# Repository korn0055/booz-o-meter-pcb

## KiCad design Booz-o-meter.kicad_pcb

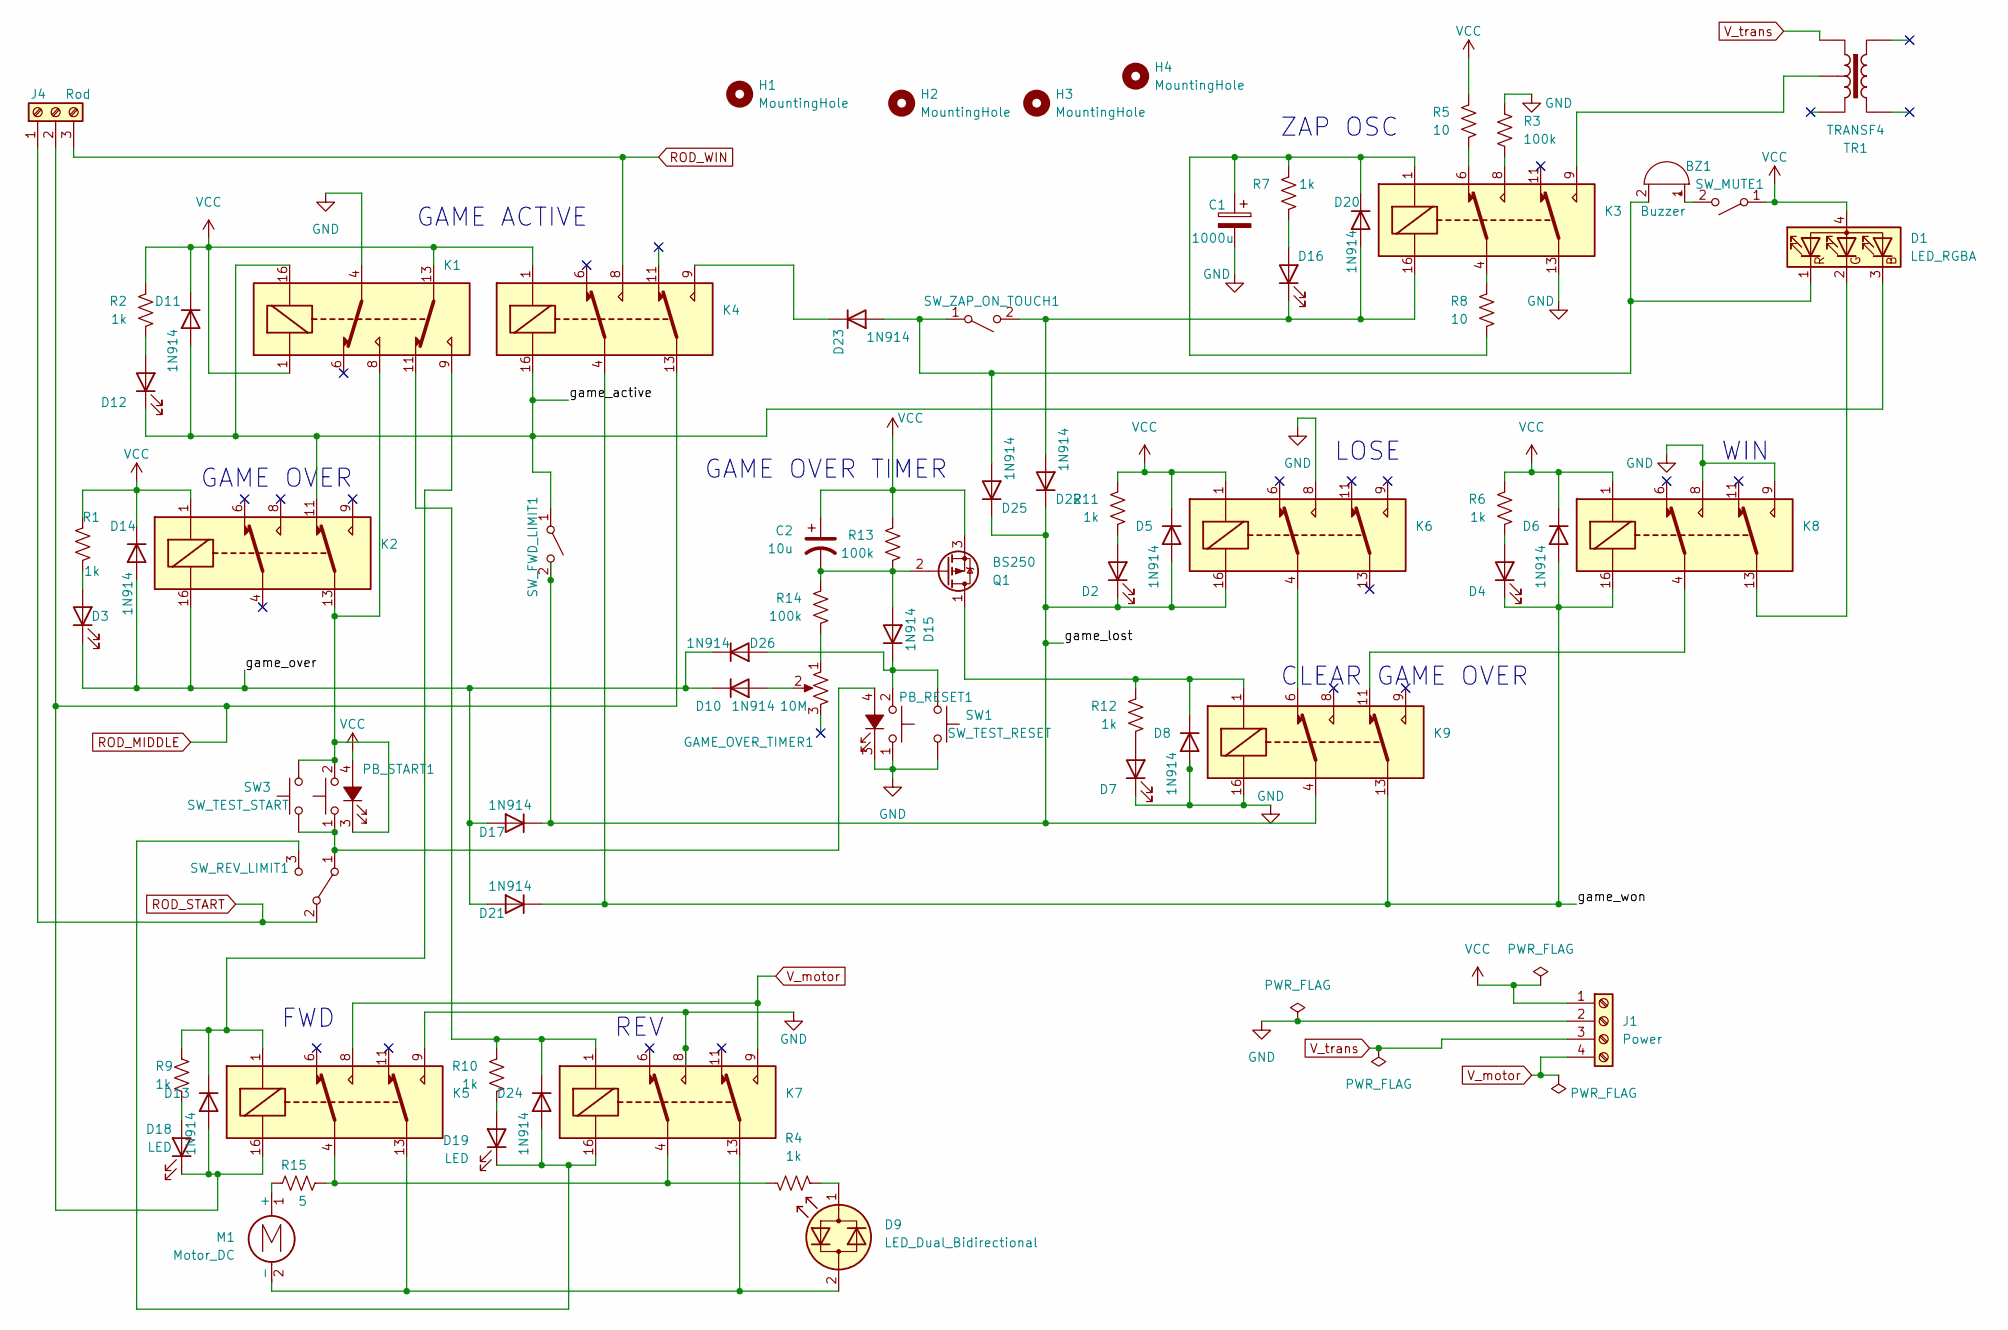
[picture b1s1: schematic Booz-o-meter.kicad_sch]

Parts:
BZ1: Buzzer; TerminalBlock_Phoenix_MKDS-1,5-2-5.08_1x02_P5.08mm_Horizont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
C1: 1000u; C_Radial_D10.0mm_H20.0mm_P5.00mm
C2: 10u; CP_Radial_Tantal_D5.0mm_P5.00mm
D1: LED_RGBA; TerminalBlock_Phoenix_MKDS-1,5-4-5.08_1x04_P5.08mm_Horizont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
D2, D3, D4, D7, D12, D16, D18, D19: LED; LED_D3.0mm
D5, D6, D8, D10, D11, D13, D14, D15, D17, D20, D21, D22, D23, D24, D25, D26: 1N914; D_DO-35_SOD27_P7.62mm_Horizontal
D9: LED_Dual_Bidirectional; LED_D5.0mm
GAME_OVER_TIMER1: 10M; Potentiometer_Bourns_3386P_Vertical
H1, H2, H3, H4: MountingHole; MountingHole_3.5mm
J1: Power; TerminalBlock_Phoenix_MKDS-1,5-4-5.08_1x04_P5.08mm_Horizont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
J4: Rod; TerminalBlock_Phoenix_MKDS-1,5-3-5.08_1x03_P5.08mm_Horizont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
K1, K2, K3, K4, K5, K6, K7, K8, K9: G5V-2; Relay_DPDT_Omron_G5V-2
M1: Motor_DC; TerminalBlock_Phoenix_MKDS-1,5-2-5.08_1x02_P5.08mm_Horizont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
PB_RESET1: SW_Push_LED; TerminalBlock_Phoenix_MKDS-1,5-4-5.08_1x04_P5.08mm_Horizont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
PB_START1: SW_Push_LED; TerminalBlock_Phoenix_MKDS-1,5-4-5.08_1x04_P5.08mm_Horizont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
Q1: BS250; TO-92_Inline
R1, R2, R4, R6, R7, R9, R10, R11, R12: 1k; R_Axial_DIN0207_L6.3mm_D2.5mm_P10.16mm_Horizontal
R3, R13, R14: 100k; R_Axial_DIN0207_L6.3mm_D2.5mm_P10.16mm_Horizontal
R5, R8: 10; R_Axial_DIN0207_L6.3mm_D2.5mm_P10.16mm_Horizontal
R15: 5; R_Axial_DIN0207_L6.3mm_D2.5mm_P10.16mm_Horizontal
SW1: SW_TEST_RESET; SW_PUSH_6mm
SW3: SW_TEST_START; SW_PUSH_6mm
SW_FWD_LIMIT1: SW_SPDT; TerminalBlock_Phoenix_MKDS-1,5-2-5.08_1x02_P5.08mm_Horizont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
SW_MUTE1: SW_SPST; TerminalBlock_Phoenix_MKDS-1,5-2-5.08_1x02_P5.08mm_Horizont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
SW_REV_LIMIT1: SW_SPDT; TerminalBlock_Phoenix_MKDS-1,5-3-5.08_1x03_P5.08mm_Horizont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
SW_ZAP_ON_TOUCH1: SW_SPST; TerminalBlock_Phoenix_MKDS-1,5-2-5.08_1x02_P5.08mm_Horizont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
TR1: TRANSF4; TerminalBlock_Phoenix_MKDS-1,5-2-5.08_1x02_P5.08mm_Horizont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

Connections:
/game_active: D1.3 (BK), D11.2 (A), D12.1 (K), K1.16, K2.11, K4.16, SW_FWD_LIMIT1.1 (A)
/game_lost: D2.1 (K), D5.2 (A), D17.1 (K), D22.1 (K), D25.1 (K), K6.16, K9.4, SW_FWD_LIMIT1.2 (B)
/game_over: D3.1 (K), D10.1 (K), D14.2 (A), D17.2 (A), D21.2 (A), D26.1 (K), K2.16
/game_won: D4.1 (K), D6.2 (A), D21.1 (K), K4.4, K8.16, K9.13
GND: C1.2, D7.1 (K), D8.2 (A), J1.2, K1.4, K3.13, K5.9, K6.8, K7.8, K8.8, K8.9, K9.16, PB_RESET1.1, PB_RESET1.3 (K), R3.1, SW1.2
unnamed: BZ1.2 (+), D1.1 (RK), D23.2 (A), D25.2 (A), SW_ZAP_ON_TOUCH1.1 (A)
unnamed: BZ1.1 (-), SW_MUTE1.2 (B)
unnamed: D1.2 (GK), K8.13
unnamed: D2.2 (A), R11.2
unnamed: D3.2 (A), R1.2
unnamed: D4.2 (A), R6.2
unnamed: D7.2 (A), R12.2
unnamed: D8.1 (K), K9.1, Q1.1 (D), R12.1
unnamed: D9.2 (AK), K5.13, K7.13, M1.2 (-)
unnamed: D9.1 (KA), R4.2
unnamed: D10.2 (A), GAME_OVER_TIMER1.2
unnamed: D12.2 (A), R2.2
unnamed: D13.1 (K), K1.9, K5.1, R9.1
unnamed: C2.2, D15.2 (A), Q1.2 (G), R13.2, R14.1
unnamed: D15.1 (K), D26.2 (A), PB_RESET1.2, SW1.1
unnamed: D16.2 (A), R7.2
unnamed: D16.1 (K), D20.2 (A), D22.2 (A), K3.16, SW_ZAP_ON_TOUCH1.2 (B)
unnamed: D18.2 (A), R9.2
unnamed: D19.2 (A), R10.2
unnamed: D19.1 (K), D24.2 (A), K7.16, SW_REV_LIMIT1.3 (C)
unnamed: C1.1, D20.1 (K), K3.1, R7.1, R8.2
unnamed: D23.1 (K), K4.9
unnamed: D24.1 (K), K1.11, K7.1, R10.1
unnamed: GAME_OVER_TIMER1.1, R14.2
unnamed: K3.4, R8.1
unnamed: K3.6, R5.2
unnamed: K3.8, R3.2
unnamed: K3.9, TR1.2
unnamed: K5.4, K7.4, R4.1, R15.2
unnamed: K6.4, K9.6
unnamed: K8.4, K9.11
unnamed: M1.1 (+), R15.1
unnamed: PB_RESET1.4 (A), PB_START1.1, SW3.2, SW_REV_LIMIT1.1 (A)
unnamed: K1.8, K2.13, PB_START1.2, PB_START1.3 (K), SW3.1
ROD_MIDDLE: D13.2 (A), D18.1 (K), J4.2, K4.13, K5.16
ROD_START: J4.1, SW_REV_LIMIT1.2 (B)
ROD_WIN: J4.3, K4.8
VCC: C2.1, D1.4 (A), D5.1 (K), D6.1 (K), D11.1 (K), D14.1 (K), J1.1, K1.1, K1.13, K2.1, K4.1, K6.1, K8.1, PB_START1.4 (A), Q1.3 (S), R1.1, R2.1, R5.1, R6.1, R11.1, R13.1, SW_MUTE1.1 (A)
V_motor: J1.4, K5.8, K7.9
V_trans: J1.3, TR1.1

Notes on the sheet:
CLEAR GAME OVER
LOSE
GAME ACTIVE
WIN
FWD
REV
GAME OVER
GAME OVER TIMER
ZAP OSC

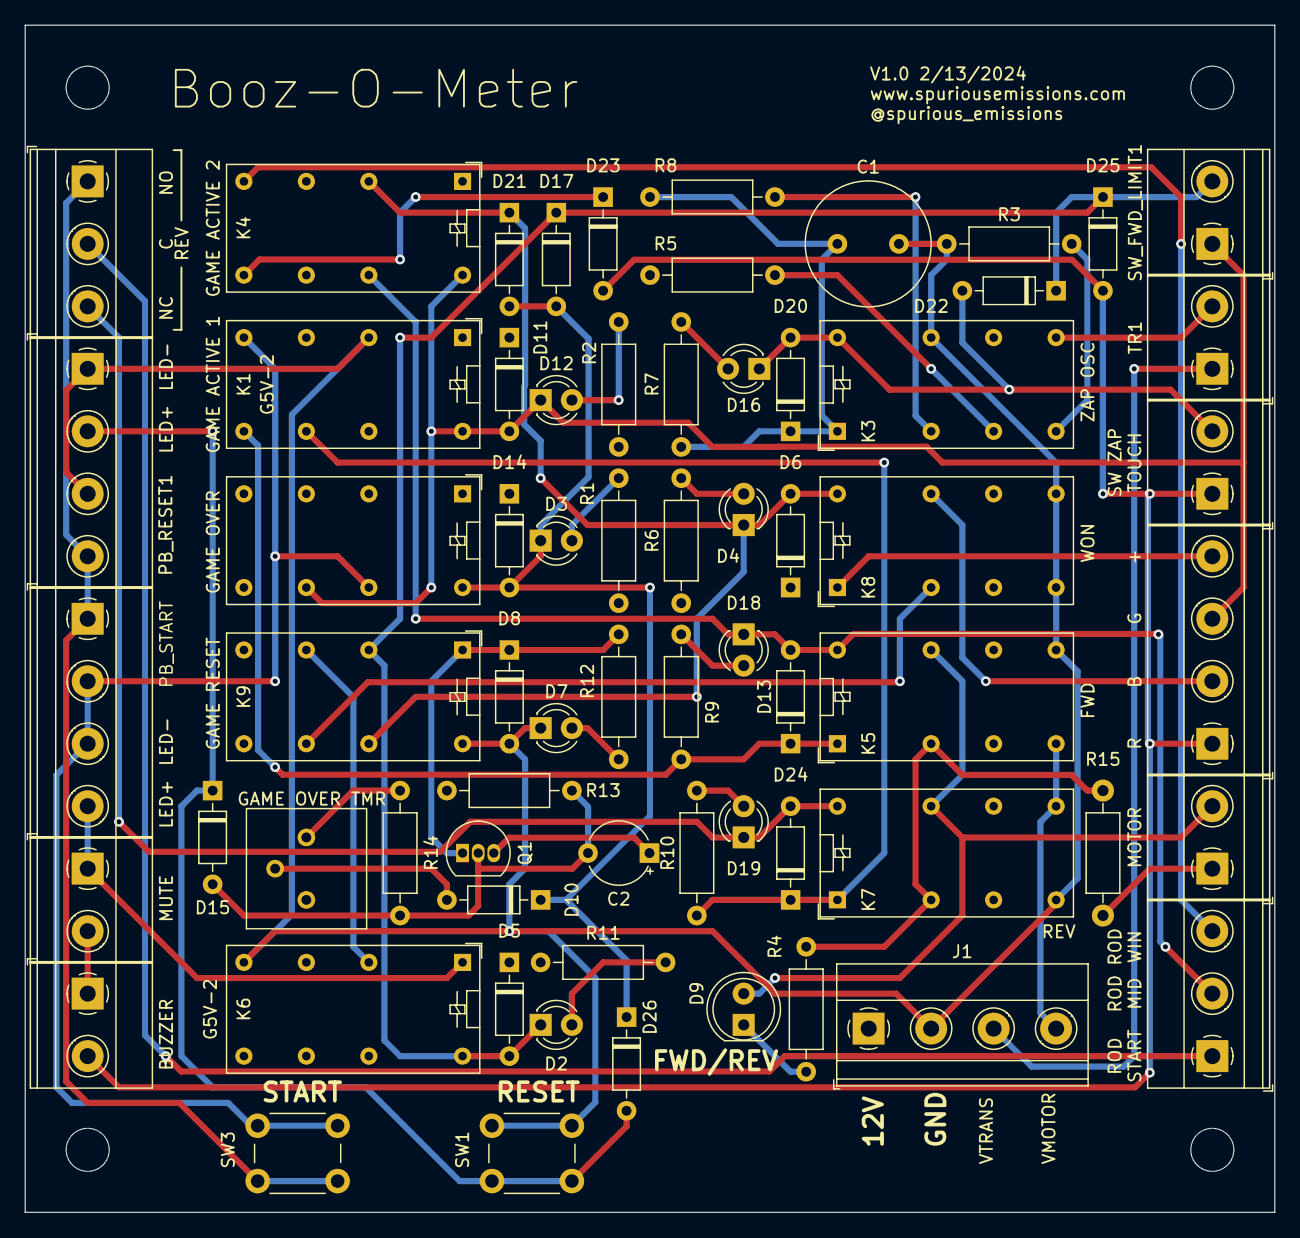
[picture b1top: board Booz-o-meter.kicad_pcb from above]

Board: 2 copper layers, 101.6 x 96.5 mm, 71 parts (0 on the bottom side), 45 nets.

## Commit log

2024-02-10 Rough schematic and component placement
2024-02-10 First pass at routing
2024-02-13 Fix zap on touch, add motor series R, clean DRC
2024-02-13 Increase resistor pitch to 0.4, add silk text
2024-02-14 Final tweaks before send out
2024-02-14 Straighten fill boundaries
2024-02-14 Actually fix fill boundaries
2024-02-14 Export V1.0 artifacts
